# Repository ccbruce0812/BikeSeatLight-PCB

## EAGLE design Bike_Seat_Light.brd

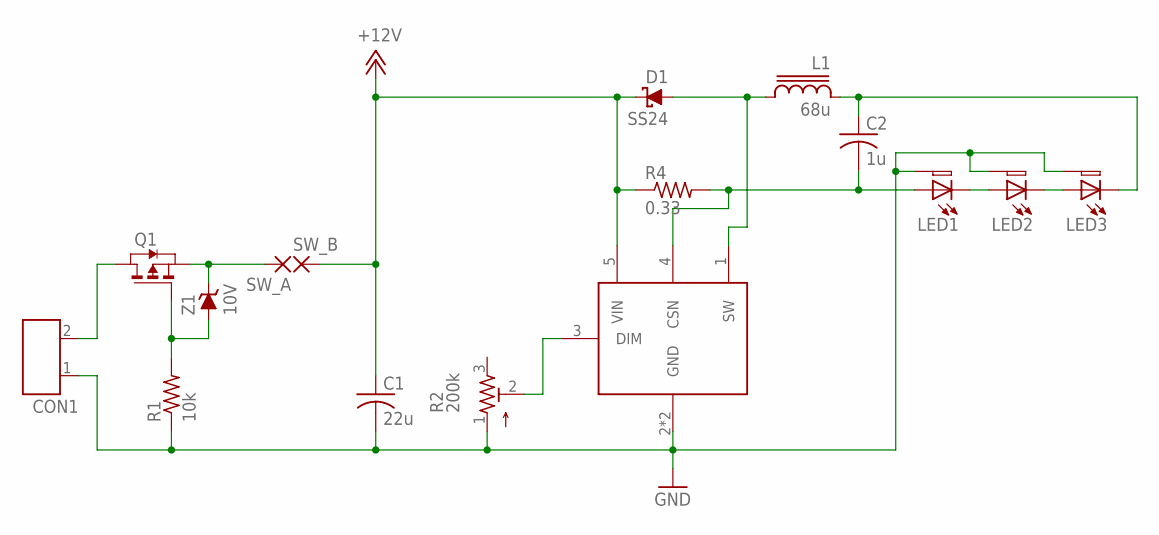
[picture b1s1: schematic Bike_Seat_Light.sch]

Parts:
C1: 22u; C1210K
C2: 1u; C0805K
CON1: KF128H
D1: SS24; DO214AC
IC1: PT4115; SOT-89-5
L1: 68u; CDRH127/LD
LED1, LED2, LED3: POWER_LED
Q1: PMOSSOT23; SOT-23
R1: 10k; R0805
R2: 200k; 3306F
R4: 0.33; R2512
SW_A: 1,6/0,9
SW_B: 1,6/0,9
Z1: 10V; SOD123

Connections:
+12V: C1.1, D1.C, IC1.5 (VIN), R4.1, SW_B.1
GND: C1.2, CON1.1, IC1.2 (GND), IC1.EX (GND), LED1.T, LED2.T, LED3.T, R1.1, R2.1
unnamed: C2.2, IC1.4 (CSN), LED1.1 (A), R4.2
unnamed: IC1.3 (DIM), R2.2
unnamed: Q1.2 (S), SW_A.1, Z1.C
unnamed: D1.A, IC1.1 (SW), L1.2
unnamed: LED1.2 (C), LED2.1 (A)
unnamed: LED2.2 (C), LED3.1 (A)
unnamed: Q1.3 (G), R1.2, Z1.A
unnamed: C2.1, L1.1, LED3.2 (C)
unnamed: CON1.2, Q1.1 (D)

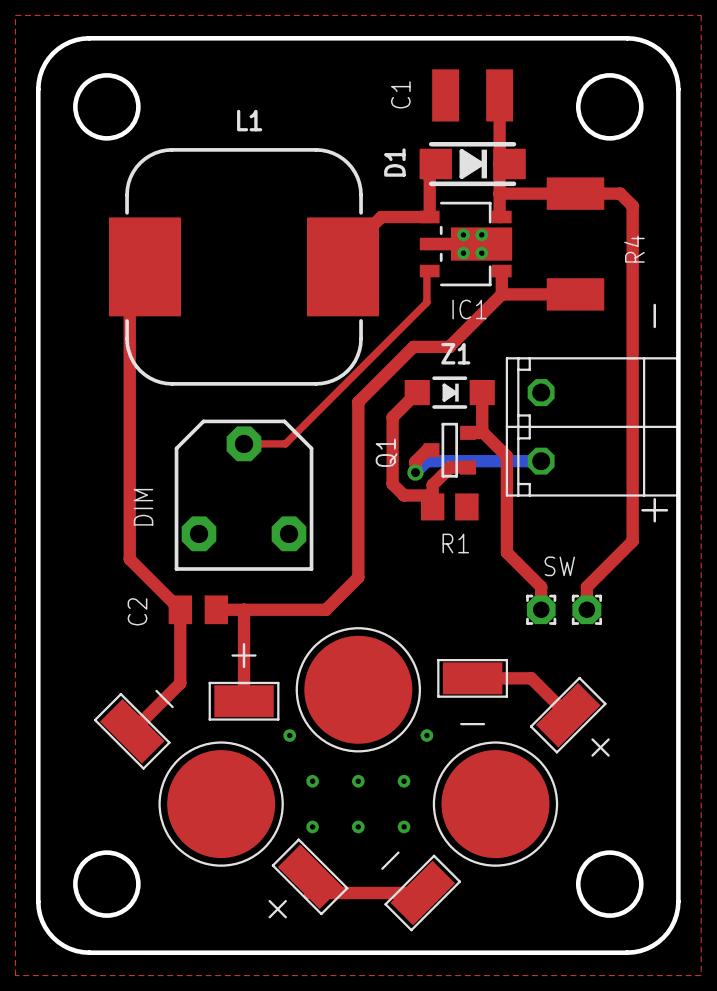
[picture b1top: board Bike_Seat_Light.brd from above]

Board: 2 copper layers, 35.6 x 50.8 mm, 16 parts (0 on the bottom side), 11 nets.

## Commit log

2018-06-24 Draft version.
